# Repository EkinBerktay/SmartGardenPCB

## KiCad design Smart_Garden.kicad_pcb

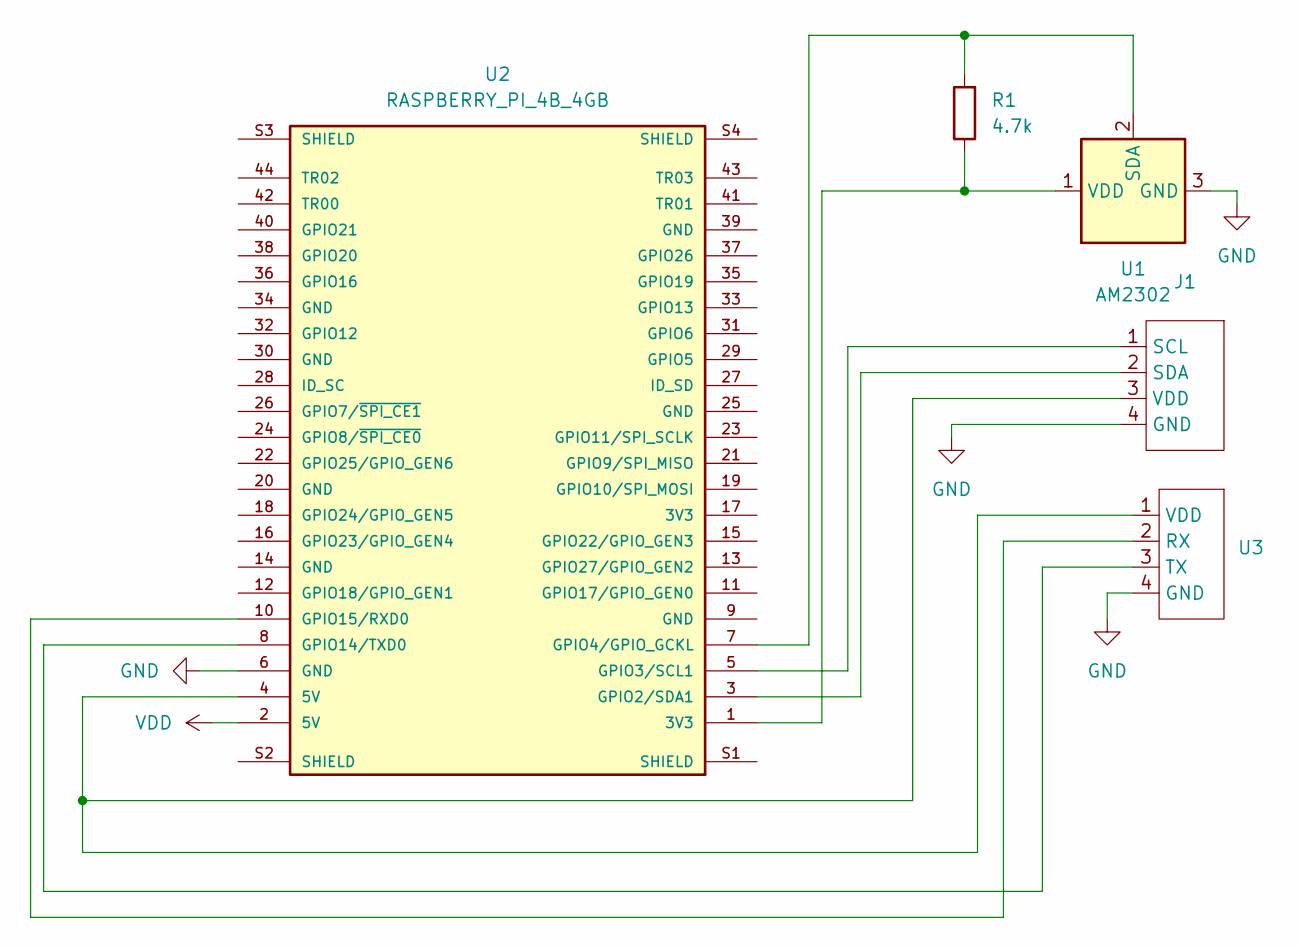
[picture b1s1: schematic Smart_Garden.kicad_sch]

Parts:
J1: 4-pinMaleSocket
R1: 4.7k; R_Axial_DIN0207_L6.3mm_D2.5mm_P7.62mm_Horizontal
U1: AM2302; ASAIR_AM2302_P2.54mm_Vertical
U2: RASPBERRY_PI_4B_4GB; MODULE_RASPBERRY_PI_4B_4GB; PARTREV 4
U3: neo-6m-module

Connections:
GND: J1.4 (GND), U1.3 (GND), U1.4 (GND), U2.6 (GND), U3.4 (GND)
unnamed: J1.1 (SCL), U2.5 (GPIO3/SCL1)
unnamed: J1.2 (SDA), U2.3 (GPIO2/SDA1)
unnamed: J1.3 (VDD), U2.4 (5V), U3.1 (VDD)
unnamed: R1.2, U1.2 (SDA), U2.7 (GPIO4/GPIO_GCKL)
unnamed: R1.1, U1.1 (VDD), U2.1 (3V3)
unnamed: U2.8 (GPIO14/TXD0), U3.3 (TX)
unnamed: U2.10 (GPIO15/RXD0), U3.2 (RX)
VDD: U2.2 (5V)

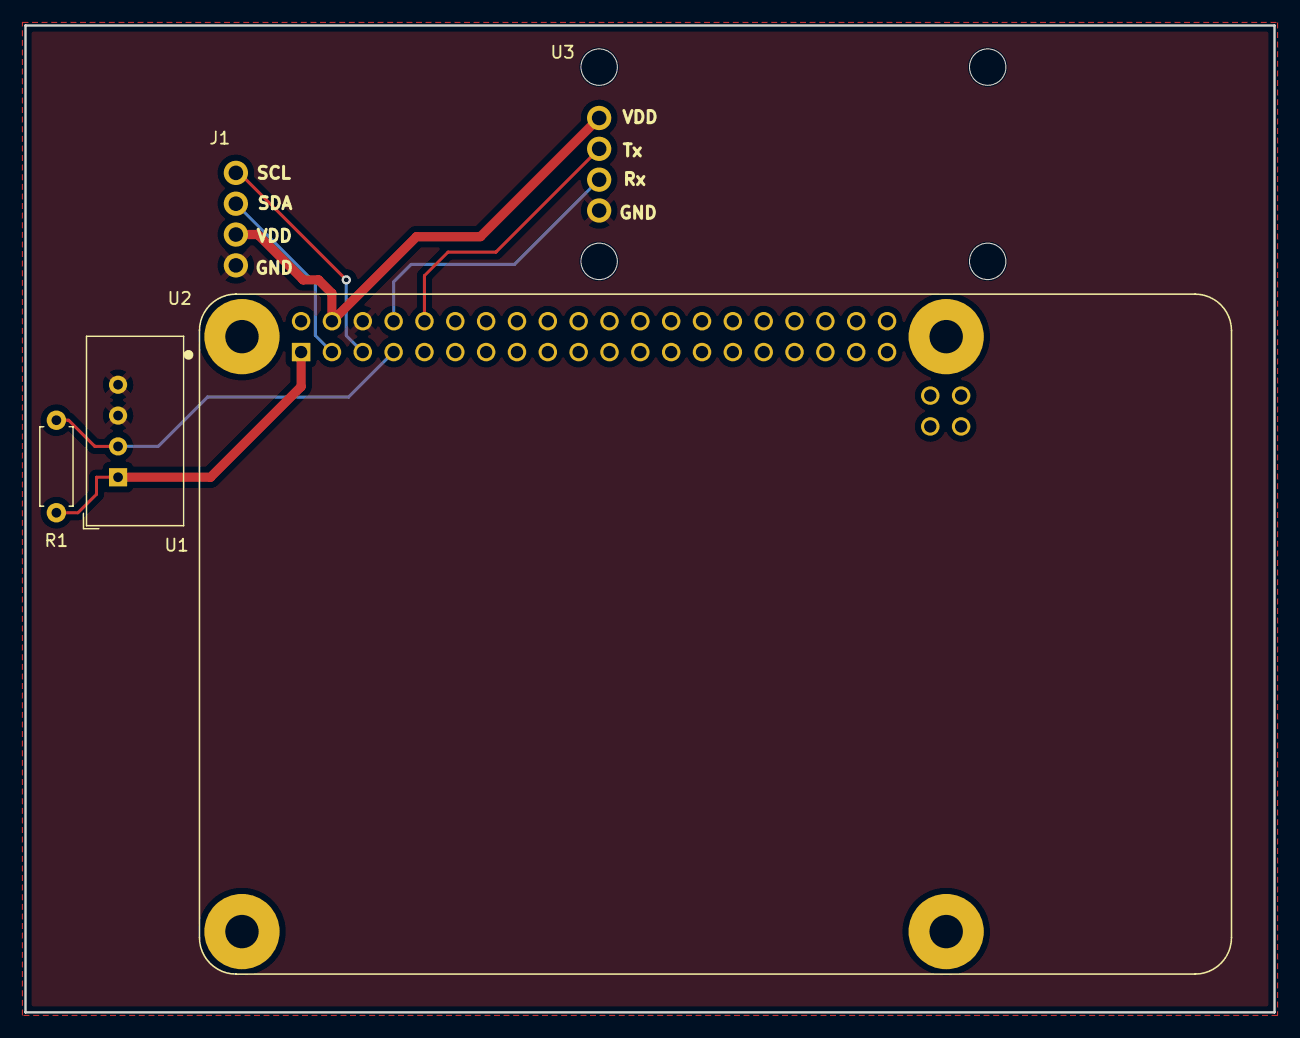
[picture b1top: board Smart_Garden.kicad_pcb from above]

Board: 2 copper layers, 102.9 x 81.3 mm, 5 parts (0 on the bottom side), 8 nets.
